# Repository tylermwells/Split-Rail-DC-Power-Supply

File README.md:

## Members
Tyler Wells, Eletrical Engineering Student (2025)
tylermwells@vt.edu

## Repo Link
<a class="button is-link" href="https://magicmirror.builders/" >https://magicmirror.builders/</a>

## Photo
{% include youtube.html video="miltuOLWDFQ" %}

## Mentor
Richard Gibbons, Electrical Engineering 2021

## Current Status
In Testing

## Project Overview

This project taking in a specific voltage range from a power supply and converts it down to positive 5 volts and negative 5 volts. 

## Educational Value Added

Buck Conveter Design
PCB Design
Power Supply Testing
Thermal Management

## Tasks

<!-- Your Text Here. See Example above -->

## Design Decisions

<!-- Your Text Here. See Example above -->

## Design Misc

<!-- Your Text Here. See Example above -->

## Steps for Documenting Your Design Process

<!-- Your Text Here. See Example above -->

## BOM + Component Cost

<!-- Your Text Here. See Example above -->

## Timeline

<!-- Your Text Here. See Example above -->

## Useful Links

<!-- Your Text Here. See Example above -->

## Log

<!-- Your Text Here. See Example above -->

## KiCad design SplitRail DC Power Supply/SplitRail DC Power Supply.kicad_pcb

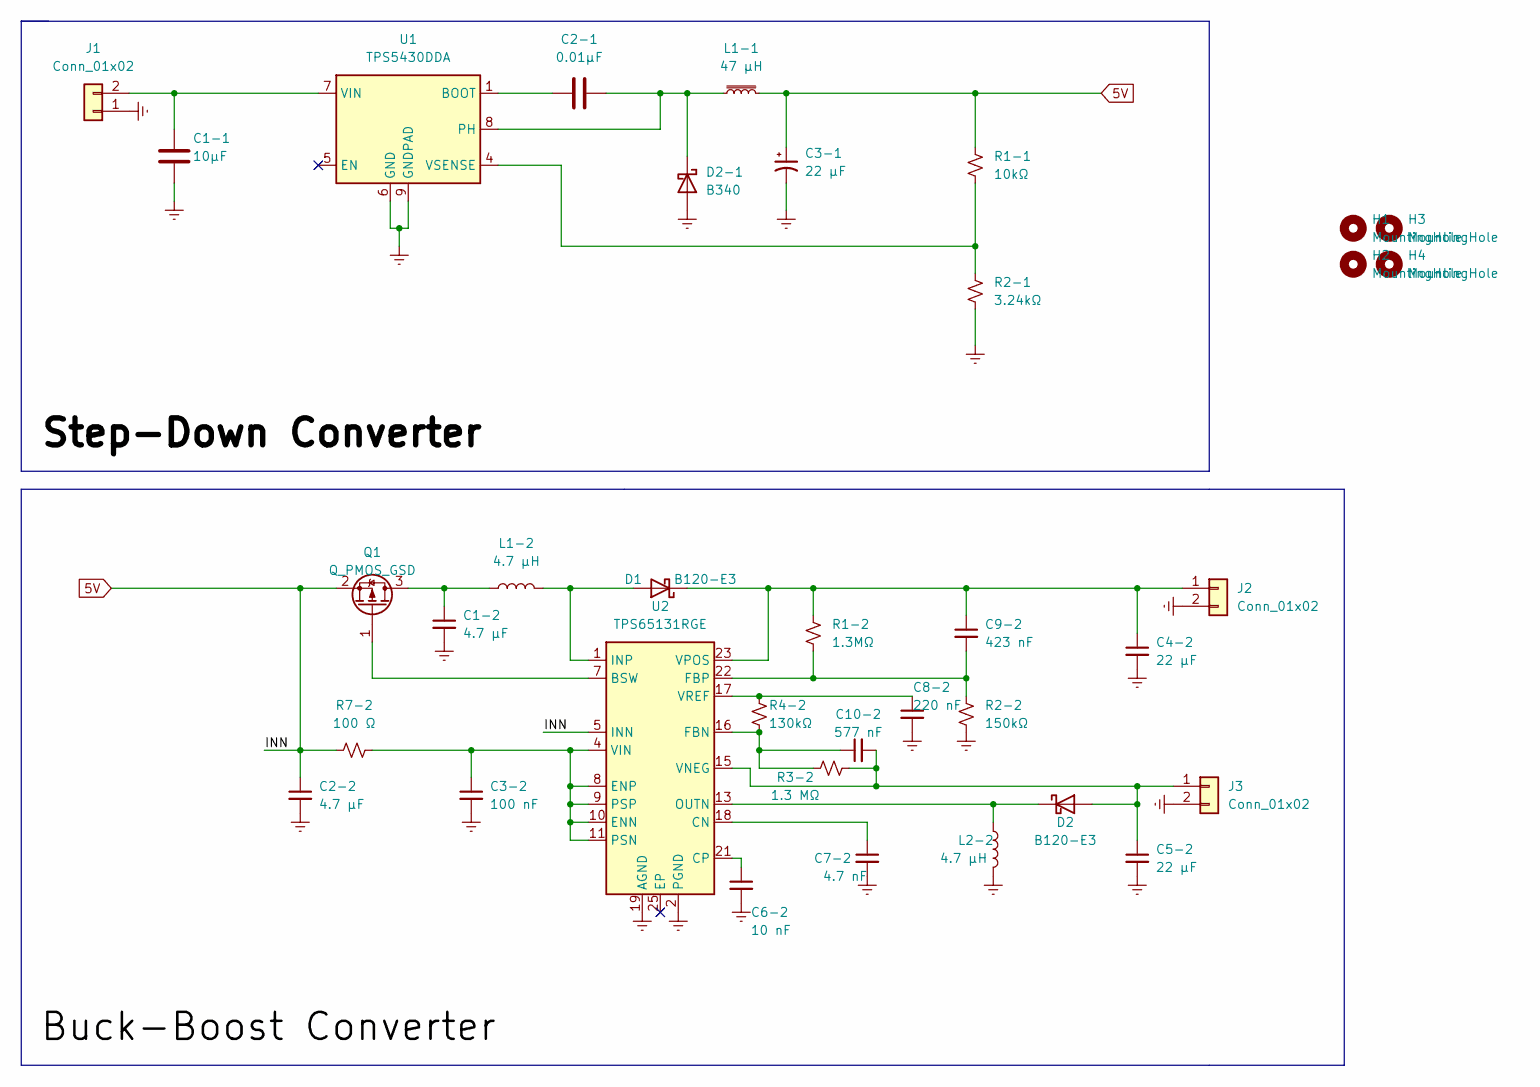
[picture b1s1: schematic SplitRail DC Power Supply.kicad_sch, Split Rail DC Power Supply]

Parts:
C1-1: 10µF; CAPC1608X90
C1-2, C2-2: 4.7 µF; C_0603_1608Metric_Pad1.08x0.95mm_HandSolder
C2-1: 0.01µF; C_0603_1608Metric_Pad1.08x0.95mm_HandSolder
C3-1, C4-2, C5-2: 22 µF; C_0603_1608Metric
C3-2: 100 nF; C_0603_1608Metric_Pad1.08x0.95mm_HandSolder
C6-2: 10 nF; C_0603_1608Metric_Pad1.08x0.95mm_HandSolder
C7-2: 4.7 nF; C_0603_1608Metric_Pad1.08x0.95mm_HandSolder
C8-2: 220 nF; C_0603_1608Metric_Pad1.08x0.95mm_HandSolder
C9-2: 423 nF; C_0603_1608Metric_Pad1.08x0.95mm_HandSolder
C10-2: 577 nF; CAPC1608X90
D1, D2: B120-E3; D_SMA
D2-1: B340; D_SMC
H1, H2, H3, H4: MountingHole; MountingHole_4.3mm_M4
J1, J2, J3: Conn_01x02; PinHeader_1x02_P2.54mm_Vertical
L1-1: 47 µH; IND_ETQP4M470KVC
L1-2, L2-2: 4.7 µH; L_6.3x6.3_H3
Q1: Q_PMOS_GSD; SOT23
R1-1: 10kΩ; R_0603_1608Metric_Pad0.98x0.95mm_HandSolder
R1-2: 1.3MΩ; R_0603_1608Metric_Pad0.98x0.95mm_HandSolder
R2-1: 3.24kΩ; R_0603_1608Metric_Pad0.98x0.95mm_HandSolder
R2-2: 150kΩ; R_0603_1608Metric_Pad0.98x0.95mm_HandSolder
R3-2: 1.3 MΩ; R_0603_1608Metric_Pad0.98x0.95mm_HandSolder
R4-2: 130kΩ; R_0603_1608Metric_Pad0.98x0.95mm_HandSolder
R7-2: 100 Ω; R_0603_1608Metric_Pad0.98x0.95mm_HandSolder
U1: TPS5430DDA; TI_SO-PowerPAD-8_ThermalVias
U2: TPS65131RGE; VQFN-24-1EP_4x4mm_P0.5mm_EP2.45x2.45mm_ThermalVias

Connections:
5V: C2-2.1, C3-1.1, L1-1.2, Q1.2 (S), R1-1.1, R7-2.1, U2.5 (INN), U2.6 (INN)
Earth: C1-1.2, C1-2.2, C2-2.2, C3-1.2, C3-2.2, C4-2.2, C5-2.2, C6-2.2, C7-2.2, C8-2.2, D2-1.2 (A), J1.1, J2.2, J3.2, L2-2.2, R2-1.2, R2-2.2, U1.6 (GND), U1.9 (GNDPAD), U2.2 (PGND), U2.3 (PGND), U2.19 (AGND)
unnamed: C1-1.1, J1.2, U1.7 (VIN)
unnamed: C1-2.1, L1-2.1, Q1.3 (D)
unnamed: C2-1.1, D2-1.1 (K), L1-1.1, U1.8 (PH)
unnamed: C2-1.2, U1.1 (BOOT)
unnamed: C3-2.1, R7-2.2, U2.4 (VIN), U2.8 (ENP), U2.9 (PSP), U2.10 (ENN), U2.11 (PSN)
unnamed: C4-2.1, C9-2.1, D1.1 (K), J2.1, R1-2.1, U2.23 (VPOS)
unnamed: C6-2.1, U2.21 (CP)
unnamed: C7-2.1, U2.18 (CN)
unnamed: C8-2.1, R4-2.1, U2.17 (VREF)
unnamed: C9-2.2, R1-2.2, R2-2.1, U2.22 (FBP)
unnamed: C10-2.1, R3-2.2, R4-2.2, U2.16 (FBN)
unnamed: C5-2.1, C10-2.2, D2.2 (A), J3.1, R3-2.1, U2.15 (VNEG)
unnamed: D1.2 (A), L1-2.2, U2.1 (INP), U2.24 (INP)
unnamed: D2.1 (K), L2-2.1, U2.13 (OUTN), U2.14 (OUTN)
unnamed: Q1.1 (G), U2.7 (BSW)
unnamed: R1-1.2, R2-1.1, U1.4 (VSENSE)

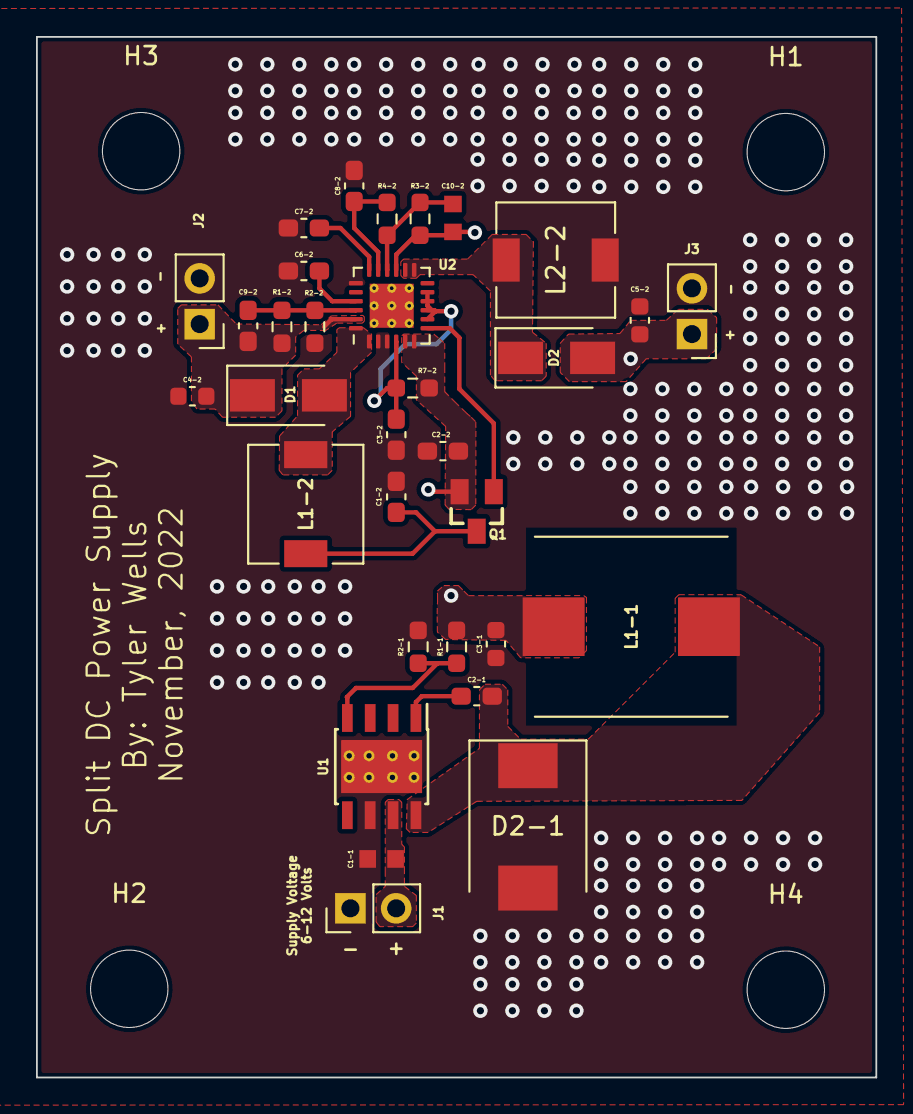
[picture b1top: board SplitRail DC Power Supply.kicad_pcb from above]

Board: 2 copper layers, 46.6 x 57.8 mm, 36 parts (0 on the bottom side), 18 nets.

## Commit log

2023-03-14 This is documentation for Split Rail DC Power Supply
2023-03-14 Adding hero image
